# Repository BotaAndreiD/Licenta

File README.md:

# CardioMed — Portable ECG Acquisition & Monitoring System

**Bachelor's Thesis · Technical University of Cluj-Napoca**
Faculty of Electronics, Telecommunications and Information Technology — 2026

A low-cost, single-lead ECG acquisition and monitoring system built around a **discrete analog front-end** instead of an integrated AFE chip — designed to meet the essential requirements of **IEC 60601-2-25** while staying affordable enough for continuous home use.

---

## Overview

Clinical-grade electrocardiographs remain largely confined to hospitals due to their cost and complexity. CardioMed explores an alternative: a fully discrete analog signal chain — individually optimized filter stages, an instrumentation amplifier, and an active common-mode rejection loop — paired with a companion desktop application that detects heartbeats in real time and generates clinical reports automatically.

Every design decision, from a single capacitor value to the ADC sample rate, is traced back to a specific requirement of the medical standard — a principle referred to throughout the project as **vertical traceability**.

## Key Results

| Parameter | Standard Requirement (IEC 60601-2-25) | Achieved |
|---|---|---|
| Input-referred noise | ≤ 30 µV p-p | **10.76 µV** |
| Passband | 50 mHz – 150 Hz | 49.67 mHz – 150.71 Hz |
| System CMRR | ≥ 89 dB | **123 – 137 dB** |
| Defibrillation protection | ≥ 5000 V | 5000 V |
| Patient fault current | ≤ 10 µA | **3.3 µA** |
| R-wave detection sensitivity (MIT-BIH) | — | **91.5%** |
| Unit cost (BOM, 1,000 units) | — | **~130 RON** |

## System Architecture

```mermaid
flowchart LR
    A[ECG Electrodes] --> B[Protection Network]
    B --> C[Right Leg Drive Loop]
    B --> D["Instrumentation Amplifier (MAX41400)"]
    D --> E["Active Filters: Bessel HPF + Twin-T Notch + Butterworth LPF"]
    E --> F["24-bit ADC (AD7124-4)"]
    F --> G["ESP32-C3 — BLE Transmission"]
    G --> H["Desktop App (C# / WPF)"]
    H --> I["PQRST Detection + Clinical Report (PDF)"]
```

- **Analog front-end** — two-stage TVS/Zener input protection, a Right Leg Drive loop for active common-mode cancellation, a MAX41400 instrumentation amplifier, and a cascade of Bessel high-pass, Twin-T notch, and Butterworth low-pass active filters.
- **Digitization & wireless link** — 24-bit AD7124-4 ADC feeding an ESP32-C3, streaming digitized ECG samples over Bluetooth Low Energy.
- **PCB** — compact 4-layer board (82×46 mm) designed in KiCad, with physically separated analog and digital domains and length-matched differential input traces.
- **Desktop application** — a C#/WPF app performing real-time PQRST detection (Pan–Tompkins-derived algorithm), computing 7 clinical parameters (heart rate, PR/QRS/QTc intervals, SDNN, R-wave amplitude, ectopic-beat count), and auto-generating signed PDF reports.
- **Validation** — the full analog chain was validated in LTSpice against a real ECG signal (MIT-BIH Normal Sinus Rhythm Database) with a realistic interference model; the detection algorithms were separately validated against the public MIT-BIH Arrhythmia and QT Databases (PhysioNet).

## Repository Structure

```
├── AchizitionareSemnal/         # Signal acquisition & analysis
├── Documentatie/                # Full thesis document & synthesis
├── ESP32BLE+InterfataDigitala/  # ESP32-C3 firmware, BLE link, and the C#/WPF monitoring app
├── PCB_REVC/                    # KiCad schematic, PCB layout, and Gerbers
├── SimulariLtspice/             # LTSpice simulations of the analog chain
├── SSET/                        # Student symposium presentation materials
└── Licenta_EA_TST_2024-2025/    # Project archive
```

## Tools & Technologies

`LTspice` · `KiCad` · `Embedded C` · `Python` · `C# / WPF` · `Bluetooth Low Energy` · `MIT-BIH / PhysioNet datasets`

## Standards

Designed against **IEC 60601-2-25** (electrocardiograph performance) and **IEC 60601-1** (basic electrical safety).

## Author

**Bota Andrei-Daniel** — Applied Electronics, Technical University of Cluj-Napoca
[GitHub](https://github.com/BotaAndreiD) · [LinkedIn](https://www.linkedin.com/in/andrei-bota-283269297/)

## Acknowledgments

Thanks to my thesis advisor and to Analog Devices, where an earlier internship shaped much of the analog design approach used in this project.

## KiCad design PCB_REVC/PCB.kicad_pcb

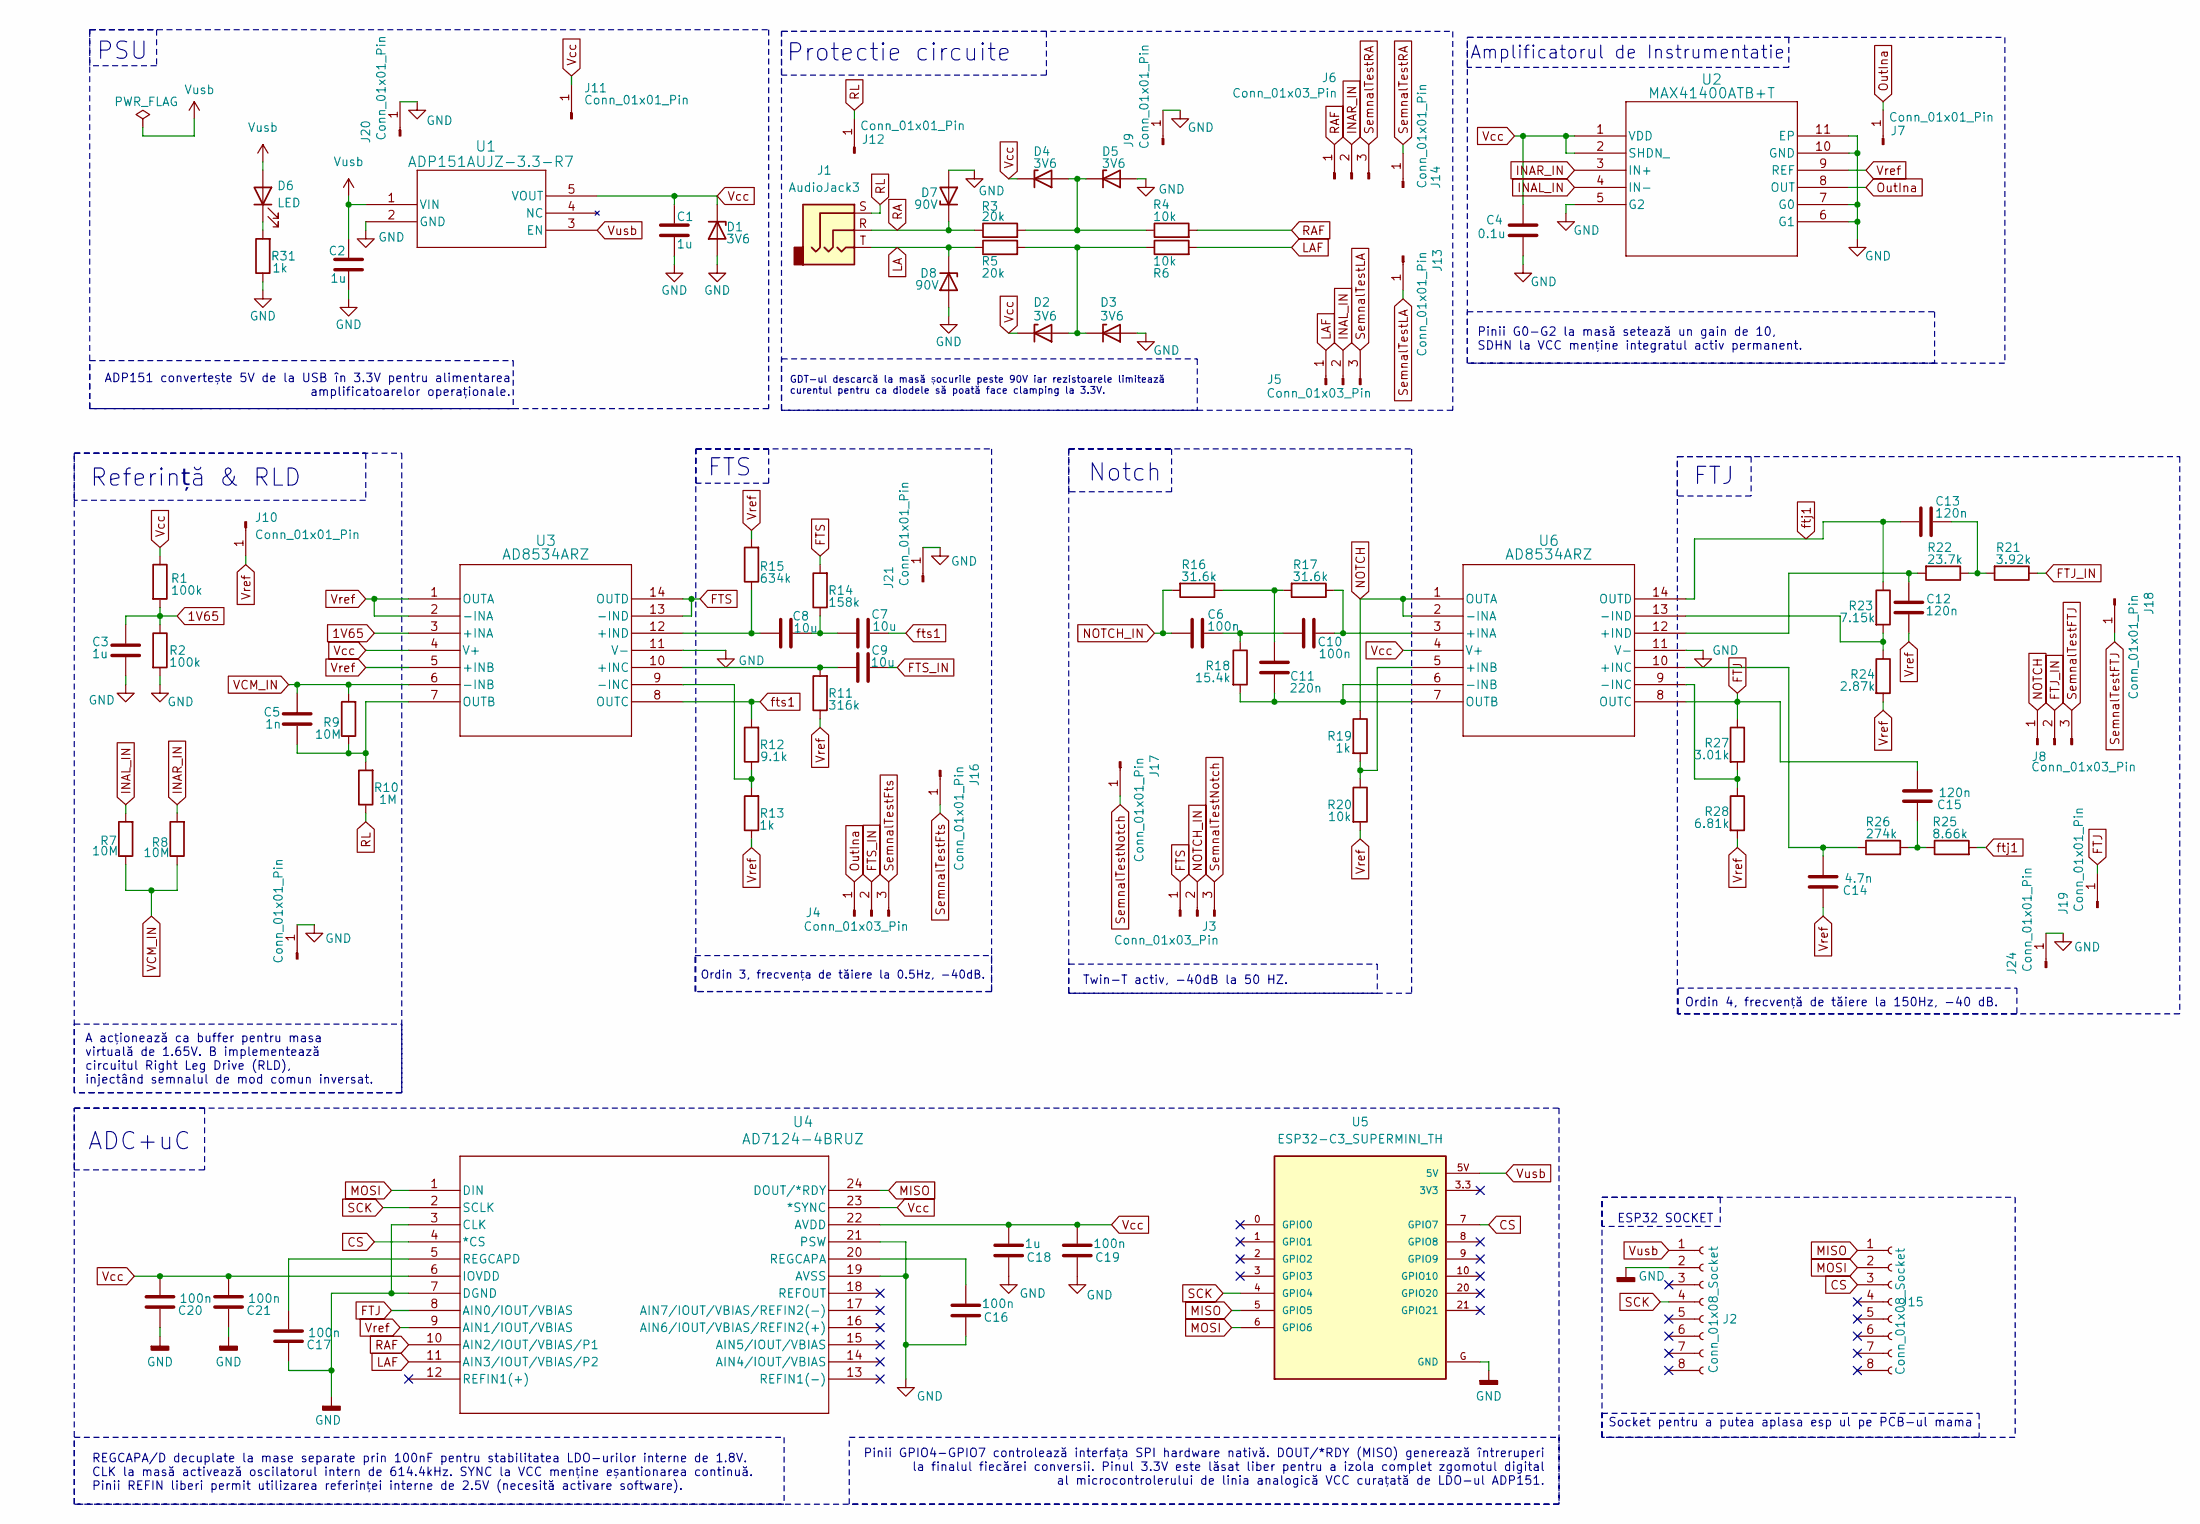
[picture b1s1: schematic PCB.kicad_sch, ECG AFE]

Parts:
C1, C2, C3, C18: 1u; C_1206_3216Metric_Pad1.33x1.80mm_HandSolder
C4: 0.1u; C_1206_3216Metric_Pad1.33x1.80mm_HandSolder
C5: 1n; C_1206_3216Metric_Pad1.33x1.80mm_HandSolder
C6, C10, C16, C17, C19, C20, C21: 100n; C_1206_3216Metric_Pad1.33x1.80mm_HandSolder
C7, C8, C9: 10u; C_1206_3216Metric_Pad1.33x1.80mm_HandSolder
C11: 220n; C_1206_3216Metric_Pad1.33x1.80mm_HandSolder
C12, C13, C15: 120n; C_1206_3216Metric_Pad1.33x1.80mm_HandSolder
C14: 4.7n; C_1206_3216Metric_Pad1.33x1.80mm_HandSolder
D1, D2, D3, D4, D5: 3V6; SOT_BZX84C3V3-7-F_DIO-L
D6: LED; LED_1206_3216Metric
D7, D8: 90V; SMBJSeries_LTF
J1: AudioJack3; Jack_3.5mm_CUI_SJ-3523-SMT_Horizontal
J2, J15: Conn_01x08_Socket; PinSocket_1x08_P2.54mm_Vertical
J3, J4, J5, J6, J8: Conn_01x03_Pin; PinHeader_1x03_P2.54mm_Vertical
J7, J9, J10, J11, J12, J13, J14, J16, J17, J18, J19, J20, J21, J22, J24: Conn_01x01_Pin; PinHeader_1x01_P2.54mm_Vertical
R1, R2: 100k; R_1206_3216Metric_Pad1.30x1.75mm_HandSolder
R3, R5: 20k; R_1206_3216Metric_Pad1.30x1.75mm_HandSolder
R4, R6, R20: 10k; R_1206_3216Metric_Pad1.30x1.75mm_HandSolder
R7, R8, R9: 10M; R_1206_3216Metric_Pad1.30x1.75mm_HandSolder
R10: 1M; R_1206_3216Metric_Pad1.30x1.75mm_HandSolder
R11: 316k; R_1206_3216Metric_Pad1.30x1.75mm_HandSolder
R12: 9.1k; R_1206_3216Metric_Pad1.30x1.75mm_HandSolder
R13, R19, R31: 1k; R_1206_3216Metric_Pad1.30x1.75mm_HandSolder
R14: 158k; R_1206_3216Metric_Pad1.30x1.75mm_HandSolder
R15: 634k; R_1206_3216Metric_Pad1.30x1.75mm_HandSolder
R16, R17: 31.6k; R_1206_3216Metric_Pad1.30x1.75mm_HandSolder
R18: 15.4k; R_1206_3216Metric_Pad1.30x1.75mm_HandSolder
R21: 3.92k; R_1206_3216Metric_Pad1.30x1.75mm_HandSolder
R22: 23.7k; R_1206_3216Metric_Pad1.30x1.75mm_HandSolder
R23: 7.15k; R_1206_3216Metric_Pad1.30x1.75mm_HandSolder
R24: 2.87k; R_1206_3216Metric_Pad1.30x1.75mm_HandSolder
R25: 8.66k; R_1206_3216Metric_Pad1.30x1.75mm_HandSolder
R26: 274k; R_1206_3216Metric_Pad1.30x1.75mm_HandSolder
R27: 3.01k; R_1206_3216Metric_Pad1.30x1.75mm_HandSolder
R28: 6.81k; R_1206_3216Metric_Pad1.30x1.75mm_HandSolder
U1: ADP151AUJZ-3.3-R7; UJ_5_ADI
U2: MAX41400ATB+T; 21-1000013_T102A2&plus_2C_ADI
U3, U6: AD8534ARZ; R_14_ADI
U4: AD7124-4BRUZ; RU-24_ADI-L
U5: ESP32-C3_SUPERMINI_TH; MODULE_ESP32-C3_SUPERMINI_TH

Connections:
1V65: C3.1, R1.2, R2.1, U3.3 (+INA)
CS: J15.3, U4.4 (*CS), U5.7 (GPIO7)
FTJ: C15.1, J19.1, R27.1, U4.8 (AIN0/IOUT/VBIAS), U6.8 (OUTC)
FTJ_IN: J8.2, R21.1
FTS: J3.1, R14.2, U3.13 (-IND), U3.14 (OUTD)
FTS_IN: C9.2, J4.2
GND: C1.2, C2.2, C3.2, C4.2, C16.2, C17.2, C18.2, C19.2, C20.2, C21.2, D1.2 (A), D3.2 (A), D5.2 (A), D7.2 (A), D8.2 (A), J2.2, J9.1, J20.1, J21.1, J22.1, J24.1, R2.2, R31.1, U1.2 (GND), U2.5 (G2), U2.6 (G1), U2.7 (G0), U2.10 (GND), U2.11 (EP), U3.11 (V-), U4.3 (CLK), U4.7 (DGND), U4.19 (AVSS), U4.21 (PSW), U5.G (GND), U6.11 (V-)
INAL_IN: J5.2, R7.2, U2.4 (IN-)
INAR_IN: J6.2, R8.2, U2.3 (IN+)
LA: D8.1 (K), J1.T, R5.1
LAF: J5.1, R6.2, U4.11 (AIN3/IOUT/VBIAS/P2)
MISO: J15.1, U4.24 (DOUT/*RDY), U5.5 (GPIO5)
MOSI: J15.2, U4.1 (DIN), U5.6 (GPIO6)
NOTCH: J8.1, R19.1, U6.1 (OUTA), U6.2 (-INA)
NOTCH_IN: C6.1, J3.2, R16.2
unnamed: C7.1, C8.2, R14.1
unnamed: C6.2, C10.1, R18.1
unnamed: C11.2, R16.1, R17.2
unnamed: C13.1, R21.2, R22.1
unnamed: C15.2, R25.1, R26.2
unnamed: D2.2 (A), D3.1 (K), R5.2, R6.1
unnamed: D4.2 (A), D5.1 (K), R3.2, R4.1
unnamed: D6.1 (K), R31.2
unnamed: C9.1, R11.2, U3.10 (+INC)
unnamed: C8.1, R15.1, U3.12 (+IND)
unnamed: R12.1, R13.2, U3.9 (-INC)
unnamed: C5.2, R9.1, R10.2, U3.7 (OUTB)
unnamed: C16.1, U4.20 (REGCAPA)
unnamed: C17.1, U4.5 (REGCAPD)
unnamed: C10.2, R17.1, U6.3 (+INA)
unnamed: R19.2, R20.1, U6.5 (+INB)
unnamed: C14.1, R26.1, U6.10 (+INC)
unnamed: C12.2, R22.2, U6.12 (+IND)
unnamed: C11.1, R18.2, U6.6 (-INB), U6.7 (OUTB)
unnamed: R27.2, R28.1, U6.9 (-INC)
unnamed: R23.2, R24.1, U6.13 (-IND)
OutIna: J4.1, J7.1, U2.8 (OUT)
RA: D7.1 (K), J1.R, R3.1
RAF: J6.1, R4.2, U4.10 (AIN2/IOUT/VBIAS/P1)
RL: J1.S, J12.1, R10.1
SCK: J2.4, U4.2 (SCLK), U5.4 (GPIO4)
SemnalTestFTJ: J8.3, J18.1
SemnalTestFts: J4.3, J16.1
SemnalTestLA: J5.3, J13.1
SemnalTestNotch: J3.3, J17.1
SemnalTestRA: J6.3, J14.1
VCM_IN: C5.1, R7.1, R8.1, R9.2, U3.6 (-INB)
Vcc: C1.1, C4.1, C18.1, C19.1, C20.1, C21.1, D1.1 (K), D2.1 (K), D4.1 (K), J11.1, R1.1, U1.5 (VOUT), U2.1 (VDD), U2.2 (SHDN_), U3.4 (V+), U4.6 (IOVDD), U4.22 (AVDD), U4.23 (*SYNC), U6.4 (V+)
Vref: C12.1, C14.2, J10.1, R11.1, R13.1, R15.2, R20.2, R24.2, R28.2, U2.9 (REF), U3.1 (OUTA), U3.2 (-INA), U3.5 (+INB), U4.9 (AIN1/IOUT/VBIAS)
Vusb: C2.1, D6.2 (A), J2.1, U1.1 (VIN), U1.3 (EN), U5.5V
ftj1: C13.2, R23.1, R25.2, U6.14 (OUTD)
fts1: C7.2, R12.2, U3.8 (OUTC)

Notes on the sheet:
Twin-T activ, -40dB la 50 HZ.
Notch
Pinii G0-G2 la masă setează un gain de 10, SDHN la VCC menține integratul activ permanent.
Referință & RLD
ADC+uC
FTS
ESP32 SOCKET
A acționează ca buffer pentru masa virtuală de 1.65V. B implementează circuitul Right Leg Drive (RLD), injectând semnalul de mod comun inversat.
Ordin 3, frecvența de tăiere la 0.5Hz, -40dB.
Ordin 4, frecvență de tăiere la 150Hz, -40 dB.
Amplificatorul de Instrumentatie
GDT-ul descarcă la masă șocurile peste 90V iar rezistoarele limitează curentul pentru ca diodele să poată face clamping la 3.3V.
PSU
FTJ
Pinii GPIO4-GPIO7 controlează interfața SPI hardware nativă. DOUT/*RDY (MISO) generează întreruperi la finalul fiecărei conversii. Pinul 3.3V este lăsat liber pentru a izola complet zgomotul digital al microcontrolerului de linia analogică VCC curațată de LDO-ul ADP151.
Socket pentru a putea aplasa esp ul pe PCB-ul mama
REGCAPA/D decuplate la mase separate prin 100nF pentru stabilitatea LDO-urilor interne de 1.8V. CLK la masă activează oscilatorul intern de 614.4kHz. SYNC la VCC menține eșantionarea continuă. Pinii REFIN liberi permit utilizarea referinței interne de 2.5V (necesită activare software).
ADP151 convertește 5V de la USB în 3.3V pentru alimentarea amplificatoarelor operaționale.
Protectie circuite

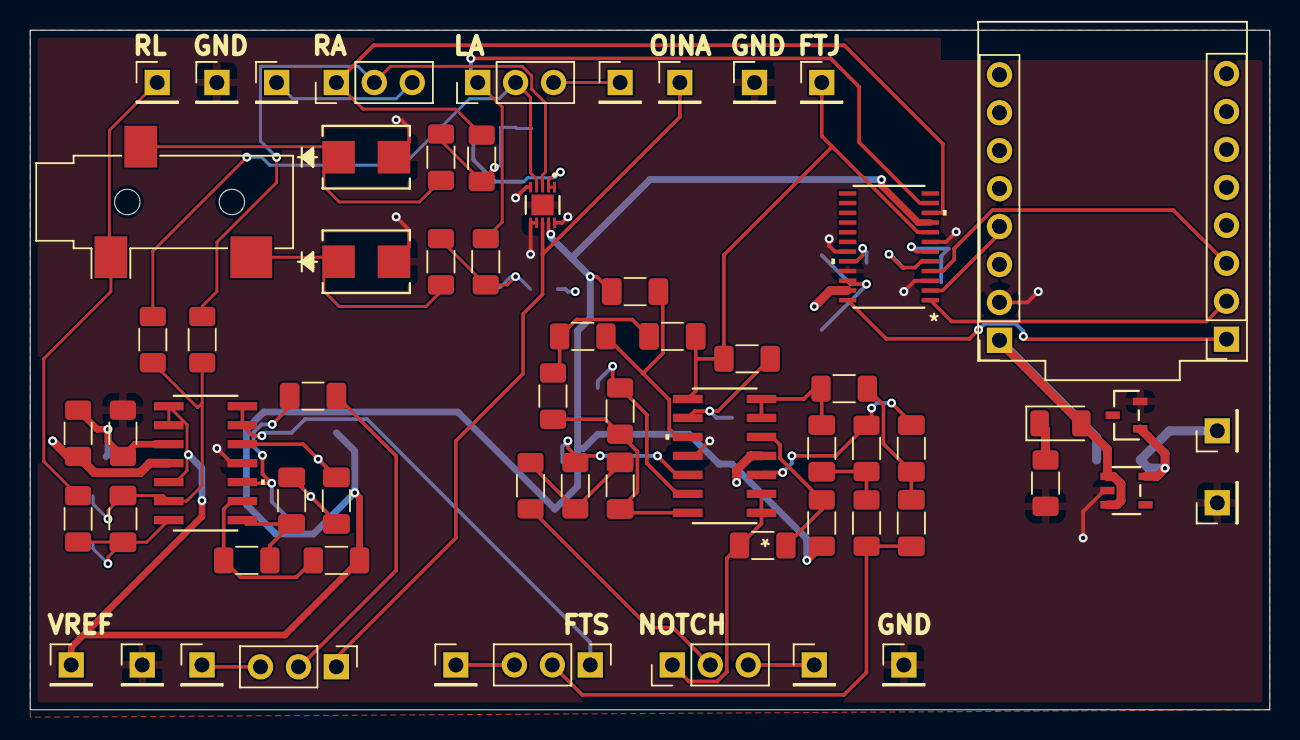
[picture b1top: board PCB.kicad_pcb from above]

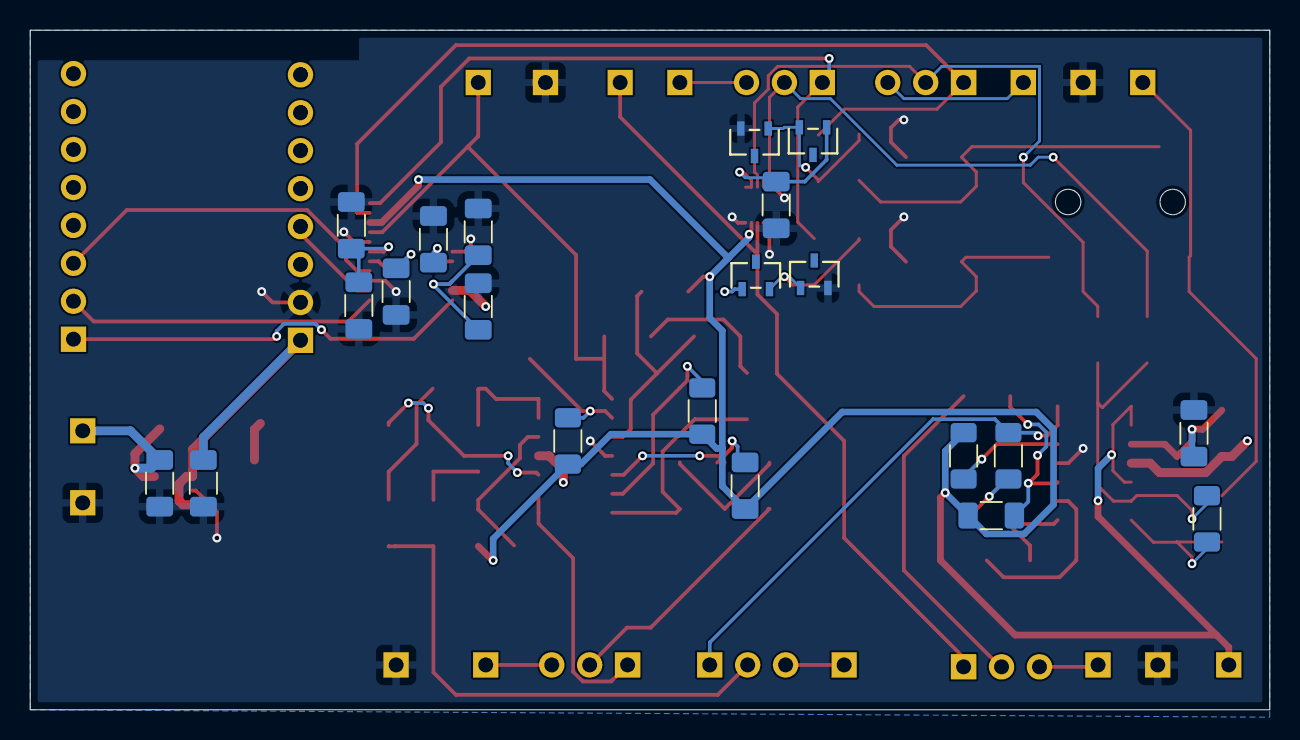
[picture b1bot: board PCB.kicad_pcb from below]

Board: 4 copper layers, 83.0 x 45.5 mm, 87 parts (21 on the bottom side), 52 nets.

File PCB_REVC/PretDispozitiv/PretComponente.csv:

Reference,Qty,Value,Footprint,Price,Field5,,,,,,,,,,,,Pret,
C1.C2.C3,3,1u,Capacitor_SMD:C_1206_3216Metric_Pad1.33x1.80mm_HandSolder,0.3388,https://ro.farnell.com/multicomp-pro/1206b105j250cp/cap-1uf-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,,,,,,,,,,,,1.0164,
C4.C6.C10.C12.C13.C15.C16.C17.C19.C20,10,0.1u,Capacitor_SMD:C_1206_3216Metric_Pad1.33x1.80mm_HandSolder,0.2541,https://ro.farnell.com/avx/12065c104jat2a/cap-0-1-f-50v-5-x7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,,,,,,,,,,,,2.541,
C5,1,1000p,Capacitor_SMD:C_1206_3216Metric_Pad1.33x1.80mm_HandSolder,0.2541,https://ro.farnell.com/multicomp-pro/1206n102j500ct/cap-1000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,,,,,,,,,,,,0.2541,
C7.C8.C9,3,10u,Capacitor_SMD:C_1206_3216Metric_Pad1.33x1.80mm_HandSolder,0.3509,https://ro.farnell.com/samsung-electro-mechanics/cl31b106kah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,,,,,,,,,,,,1.0527,
C11,1,0.22u,Capacitor_SMD:C_1206_3216Metric_Pad1.33x1.80mm_HandSolder,0.3388,https://ro.farnell.com/avx/12065c224jat2a/cap-0-22-f-50v-5-x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,,,,,,,,,,,,0.3388,
C14,1,4700p,Capacitor_SMD:C_1206_3216Metric_Pad1.33x1.80mm_HandSolder,0.2541,https://ro.farnell.com/kemet/c1206c472j5ractu/cap-4700pf-50v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,,,,,,,,,,,,0.2541,
C18.C21,2,1u,Capacitor_Tantalum_SMD:CP_EIA-3216-18_Kemet-A_HandSolder,0.6776,https://ro.farnell.com/kemet/t491a105k025at/cap-1-f-25v-10-1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,,,,,,,,,,,,1.3552,
D1.D2.D3.D4.D5,5,3V6,footprints:SOT_BZX84C3V3-7-F_DIO-L,0.2662,https://ro.farnell.com/diodes-inc/bzx84c3v6/diode-zener-3-6v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,,,,,,,,,,,,1.331,
D6,1,LED,LED_SMD:LED_1206_3216Metric,0.3388,https://ro.farnell.com/qt-brightek/qblp650-o/led-orange-1206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,,,,,,,,,,,,0.3388,
D7.D8,2,90V,footprints:SMBJSeries_LTF,0.7744,https://ro.farnell.com/taiwan-semiconductor/smbj90a/tvs-diod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,,,,,,,,,,,,1.5488,
J1,1,AudioJack3,Connector_Audio:Jack_3.5mm_CUI_SJ-3523-SMT_Horizontal,3.1097,https://ro.farnell.com/same-sky/sj-3523-smt-tr/phone-audio-c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,,,,,,,,,,,,3.1097,
J2.J15,2,Conn_01x08_Socket,Connector_PinSocket_2.54mm:PinSocket_1x08_P2.54mm_Vertical,5.0699,https://ro.farnell.com/harwin/m20-7820842/connector-rcpt-8po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,,,,,,,,,,,,10.1398,
J3.J4.J5.J6.J8,5,Conn_01x03_Pin,Connector_PinHeader_2.54mm:PinHeader_1x03_P2.54mm_Vertical,5.203,https://ro.farnell.com/harwin/m20-9774046/connector-header-4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,,,,,,,,,,,,0,
J7.J9.J10.J11.J12.J13.J14.J16.J17.J18.J19.J20.J21.J22.J24,15,Conn_01x01_Pin,Connector_PinHeader_2.54mm:PinHeader_1x01_P2.54mm_Vertical,5.203,https://ro.farnell.com/harwin/m20-9774046/connector-header-4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,,,,,,,,,,,,5.203,
R1.R2,2,100k,Resistor_SMD:R_1206_3216Metric_Pad1.30x1.75mm_HandSolder,0.7018,https://ro.farnell.com/yageo/rt1206brd07100kl/res-100k-0-1-0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,,,,,,,,,,,,1.4036,
R3.R5,2,20k,Resistor_SMD:R_1206_3216Metric_Pad1.30x1.75mm_HandSolder,0.0484,https://ro.farnell.com/multicomp-pro/mcwr12x2002ftl/res-20k-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,,,,,,,,,,,,0.0968,
R4.R6.R20,3,10k,Resistor_SMD:R_1206_3216Metric_Pad1.30x1.75mm_HandSolder,0.6655,https://ro.farnell.com/yageo/rt1206brd0710kl/res-10k-0-1-0-2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,,,,,,,,,,,,1.9965,
R7.R8.R9,3,10M,Resistor_SMD:R_1206_3216Metric_Pad1.30x1.75mm_HandSolder,0.4961,https://ro.farnell.com/vishay/crcw120610m0dheap/res-aec-q200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,,,,,,,,,,,,1.4883,
R10,1,1M,Resistor_SMD:R_1206_3216Metric_Pad1.30x1.75mm_HandSolder,0.7502,https://ro.farnell.com/koa/rn73r2bttd1004b25/res-1m-0-25w-me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,,,,,,,,,,,,0.7502,
R11,1,316k,Resistor_SMD:R_1206_3216Metric_Pad1.30x1.75mm_HandSolder,0.0726,https://ro.farnell.com/yageo/rc1206fr-07316kl/res-316k-1-0-2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,,,,,,,,,,,,0.0726,
R12,1,9.1k,Resistor_SMD:R_1206_3216Metric_Pad1.30x1.75mm_HandSolder,0.0484,https://ro.farnell.com/multicomp-pro/mcwr12x9101ftl/res-9k1-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,,,,,,,,,,,,0.0484,
R13.R19.R31,3,1k,Resistor_SMD:R_1206_3216Metric_Pad1.30x1.75mm_HandSolder,0.0484,https://ro.farnell.com/multicomp-pro/wr12x1001ftl/res-1k-1-2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,,,,,,,,,,,,0.1452,
R14,1,158k,Resistor_SMD:R_1206_3216Metric_Pad1.30x1.75mm_HandSolder,0.1815,https://ro.farnell.com/panasonic/erj8enf1583v/res-158k-1-0-2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,,,,,,,,,,,,0.1815,
R15,1,620k,Resistor_SMD:R_1206_3216Metric_Pad1.30x1.75mm_HandSolder,0.121,https://ro.farnell.com/vishay/crcw1206620kfkea/res-620k-1-0-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,,,,,,,,,,,,0.121,
R16.R17,2,31.6k,Resistor_SMD:R_1206_3216Metric_Pad1.30x1.75mm_HandSolder,1.2221,https://ro.farnell.com/panasonic/era8aeb3162v/res-31k6-0-1-0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,,,,,,,,,,,,2.4442,
R18,1,15.4k,Resistor_SMD:R_1206_3216Metric_Pad1.30x1.75mm_HandSolder,0.121,https://ro.farnell.com/vishay/crcw120615k4fkea/res-15k4-1-0-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,,,,,,,,,,,,0.121,
R21,1,3.92k,Resistor_SMD:R_1206_3216Metric_Pad1.30x1.75mm_HandSolder,0.0726,https://ro.farnell.com/yageo/rc1206fr-073k92l/res-3k92-1-0-2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,,,,,,,,,,,,0.0726,
R22,1,23.7k,Resistor_SMD:R_1206_3216Metric_Pad1.30x1.75mm_HandSolder,0.0605,https://ro.farnell.com/yageo/rc1206fr-0723k7l/res-23k7-1-0-2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,,,,,,,,,,,,0.0605,
R23,1,7.15k,Resistor_SMD:R_1206_3216Metric_Pad1.30x1.75mm_HandSolder,0.0726,https://ro.farnell.com/yageo/rc1206fr-077k15l/res-7k15-1-0-2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,,,,,,,,,,,,0.0726,
R24,1,2.87k,Resistor_SMD:R_1206_3216Metric_Pad1.30x1.75mm_HandSolder,0.0726,https://ro.farnell.com/yageo/rc1206fr-072k87l/res-2k87-1-0-2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,,,,,,,,,,,,0.0726,
R25,1,8.66k,Resistor_SMD:R_1206_3216Metric_Pad1.30x1.75mm_HandSolder,0.0726,https://ro.farnell.com/yageo/rc1206fr-078k66l/res-8k66-1-0-2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,,,,,,,,,,,,0.0726,
R26,1,274k,Resistor_SMD:R_1206_3216Metric_Pad1.30x1.75mm_HandSolder,0.0726,https://ro.farnell.com/yageo/rc1206fr-07274kl/res-274k-1-0-2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,,,,,,,,,,,,0.0726,
R27,1,3.01k,Resistor_SMD:R_1206_3216Metric_Pad1.30x1.75mm_HandSolder,0.0605,https://ro.farnell.com/bourns/cr1206-fx-3011elf/res-3k01-1-1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,,,,,,,,,,,,0.0605,
R28,1,6.81k,Resistor_SMD:R_1206_3216Metric_Pad1.30x1.75mm_HandSolder,0.0726,https://ro.farnell.com/yageo/rc1206fr-076k81l/res-6k81-1-0-2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,,,,,,,,,,,,0.0726,
U1,1,ADP151AUJZ-3.3-R7,footprints:UJ_5_ADI,4.6464,https://ro.farnell.com/analog-devices/adp151aujz-3-3-r7/ldo-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,,,,,,,,,,,,4.6464,
U2,1,MAX41400ATB+T,footprints:21-1000013_T102A2&plus_2C_ADI,11.3861,https://ro.farnell.com/analog-devices/max41400atb-t/instrume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,,,,,,,,,,,,11.3861,
U3.U6,2,AD8534ARZ,footprints:R_14_ADI,6.897,https://ro.farnell.com/analog-devices/ad8534arz/op-amp-3mhz-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,,,,,,,,,,,,13.794,
U4,1,AD7124-4BRUZ,footprints:RU-24_ADI-L,51.3887,https://ro.farnell.com/analog-devices/ad7124-4bruz/adc-24bit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,,,,,,,,,,,,51.3887,
U5,1,ESP32-C3_SUPERMINI_TH,footprints:MODULE_ESP32-C3_SUPERMINI_TH,9.4,https://www.alibaba.com/product-detail/ESP32-C3-Super-Mini-D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,,,,,,,,,,,,9.4,
,,,,,,,,,,,,,,,,,128.5245,",+1.85 lei per pcb"
,,,,,,,,,,,,,,,,=,130LEI,

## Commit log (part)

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2025-10-21 Am adaugat primele articole aferente lucrarii de licenta
2025-11-11 Adaugat inca 2 link-uri utile
2025-11-12 Adaugat Articol
2025-11-19 Motivarea alegerii INA
2025-12-21 Adaugat Folder aferetent simulari si folder cum am preluat datele pentru a simula un semnal ekg in Ltspice
2025-12-21 Track EKG signal with Git LFS
2025-12-31 Adaugat simulari aferente in LTSpice
2026-01-03 Move large EKG signal file to Git LFS
2026-01-10 Adaugat simulari pentru a demonstra functionalitatea circuitului
2026-01-12 Adaugat simulari aferente LTspice pentru AD8232
2026-02-13 Adaugat simulari
2026-03-01 -Modificat simularea "AchizitionareSemnal" din cauza unor mici erori intampinate -Adaugat folder folosit in Mendeley Cite pentru a cita in documentatie -Adaugat simularea aferenta filtrului Notch
2026-03-01 add EKG signals via Git LFS
2026-03-04 -Adaugat simulari extra pentru a dovedi functionalitatea sistemului de achizitie -Simulare pentru zgomotul de 50hz -Simulare pentru offset-ul generat de electrozi -Simulare pentru a dovedi functionar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
2026-03-06 Adaugat simulari aferente pentru a indeplini standardele medicale pentru -Simulare protectie pentru supratensiune de la defibrilator -Adaugat simulare de stress test in care au fost modelate toate ne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
2026-03-12 Reorganizat foldere pentru o intelegere mai buna
2026-03-23 Add project files with LFS for large EKG data
2026-03-24 Modificat RLD circuit
2026-03-30 Adaugat simulari care sa reprezinte schema bloc
2026-04-01 Remove large simulation files and fix gitignore
2026-04-06 Adaugat fisierele aferente PCB
2026-04-07 Rezolvat conflicte: păstrat versiunea locală
2026-04-07 Modificat pcb ul cu scopul de a adauga test point uri
2026-04-08 Modificat pcb
2026-04-08 Remodificat un pin de testpoint
2026-04-08 Sters .zip pentru a testa jlcpcb
2026-04-10 Ultimele modificari a iteratiei A pentru PCB inainte de comanda
2026-05-05 Adaugat simulari pentru a testa impacul tolerantei asupra sistemului de achizitie
2026-05-11 Adaugat modificari
2026-05-11 Modificat simulari + adaugat ppt pentru SSET2026
2026-06-09 Adaugat adc si uc la pcb
2026-06-11 Modificat la ultima iteratie PCB-ul
2026-06-16 Adaugat ultima iteratie a PCB-ului si realizat interfata grafica
2026-06-20 Adaugat cod pentru transmiterea BLE a datelor ecg
2026-06-21 Modificat interfata si adaugat compatibilitae BLE esp32-c3 supermini
2026-06-29 Adaugat PanTompkins detectie
2026-06-29 Adaugat validarea agloritmilor de calcul a parametrilor ecg din interfata
